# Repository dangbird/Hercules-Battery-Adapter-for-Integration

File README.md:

# Hercules-Battery-Adapter-for-Integration
Hercules Battery Adapter for Integration

Remix of https://www.thingiverse.com/thing:7120865

Converted the original models above into CAD workable files using F3D Prismatic conversion tool.

Modified to fit new batteries (they have a tab now that doesn't work with the original model) and removed mounting screw holes.

Completely re-worked the back plate and connection mechanism to use a PCB with spade terminals (KEYSTONE 1266) to connect to the battery terminals and screw lugs for the output (KEYSTONE 7770).

All these modifications were done to allow easy integration into other CAD projects / models.
I'm working on a DIY car diagnostic tool that needed a simple to use battery and this should be perfect for that use case.

There is a 3D photogrammetry scan of a 2.5AH battery included that I used to sanity-check the model.

Much thanks to the original creator of the model! Everything was a perfect fit except the weird tab I previously mentioned.

NOTE: The PCB has not been test-fitted into this model. I got the slowest/cheapest shipping method from JLCPCB, so modifications may be made in the near future.

The main piece should be printed vertically with no supports. I used mouse ears on the 4 corners and a smaller mouse ear on the small middle part (see [Slicer-Ears] 3mf file for example).

The back plate should be printed with the flat side touching the bed, no supports for this either.

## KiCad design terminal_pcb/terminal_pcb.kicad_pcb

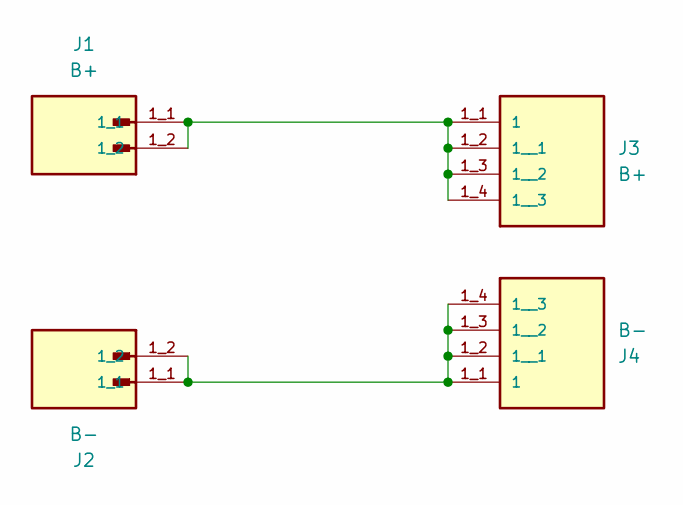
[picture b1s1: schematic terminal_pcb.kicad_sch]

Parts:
J1: B+; KEYSTONE_1266; PARTREV C
J2: B-; KEYSTONE_1266; PARTREV C
J3: B+; KEYSTONE-7770; PARTREV B
J4: B-; KEYSTONE-7770; PARTREV B

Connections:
unnamed: J1.1_1, J1.1_2, J3.1_1 (1), J3.1_2 (1__1), J3.1_3 (1__2), J3.1_4 (1__3)
unnamed: J2.1_1, J2.1_2, J4.1_1 (1), J4.1_2 (1__1), J4.1_3 (1__2), J4.1_4 (1__3)

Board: 2 copper layers, 4 parts (2 on the bottom side), 2 nets, no tracks yet.

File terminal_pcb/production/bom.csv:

Designator,Footprint,Quantity,Value,LCSC Part #
J1,KEYSTONE_1266,1,B+,
J2,KEYSTONE_1266,1,B-,
J3,KEYSTONE-7770,1,B+,
J4,KEYSTONE-7770,1,B-,

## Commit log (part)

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2026-02-15 commited all files
2026-02-16 added GCODE file type to .gitignore
